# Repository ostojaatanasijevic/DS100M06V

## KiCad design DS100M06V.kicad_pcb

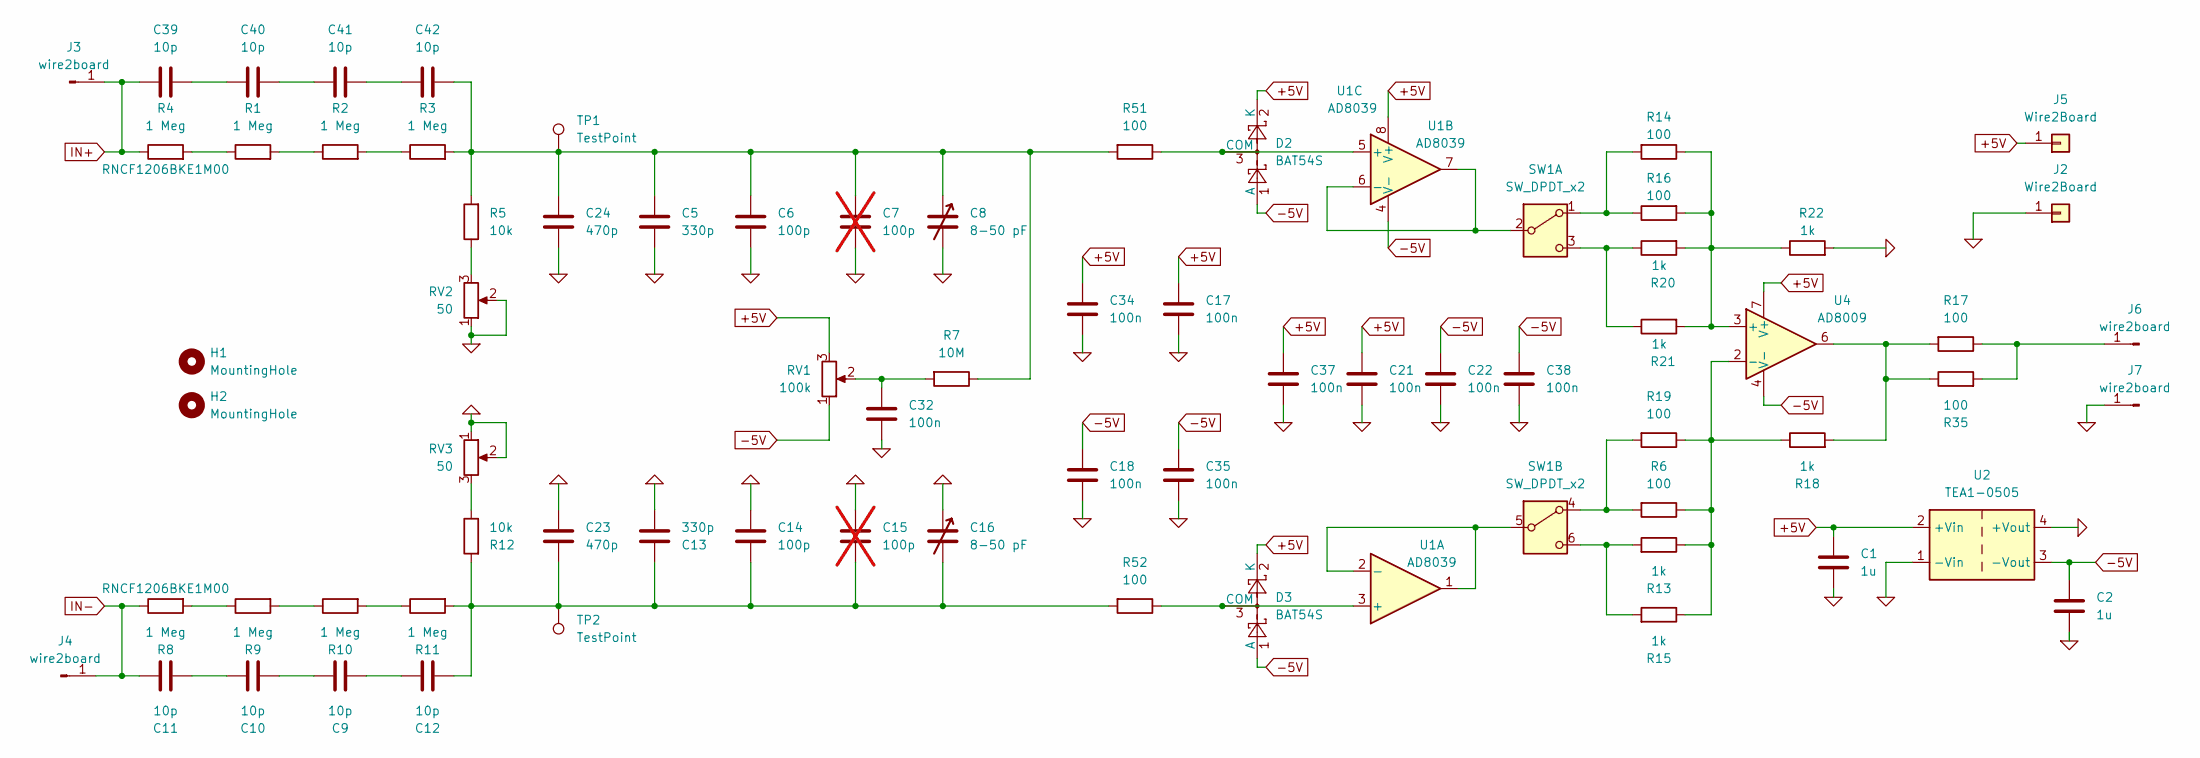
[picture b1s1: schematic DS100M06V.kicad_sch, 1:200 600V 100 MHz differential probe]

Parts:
C1, C2: 1u; R_0603_1608Metric_Pad0.98x0.95mm_HandSolder
C5, C13: 330p; R_0603_1608Metric_Pad0.98x0.95mm_HandSolder
C6, C14: 100p; R_0603_1608Metric_Pad0.98x0.95mm_HandSolder
C7, C15: 100p; R_0603_1608Metric_Pad0.98x0.95mm_HandSolder; not fitted
C8, C16: 8-50 pF; C_Trimmer_Murata_TZB4-A
C9, C10, C11, C12, C39, C40, C41, C42: 10p; R_0805_2012Metric
C17, C18, C21, C22, C32, C34, C35, C37, C38: 100n; R_0603_1608Metric_Pad0.98x0.95mm_HandSolder
C23, C24: 470p; R_0603_1608Metric_Pad0.98x0.95mm_HandSolder
D2, D3: BAT54S; SOT-23
H1, H2: MountingHole; MountingHole_3.2mm_M3
J2, J5: Wire2Board; SolderWire-0.127sqmm_1x01_D0.48mm_OD1mm
J3, J4, J6, J7: wire2board; SolderWire-0.25sqmm_1x01_D0.65mm_OD1.7mm
R1, R2, R3, R9, R10, R11: 1 Meg; R_1206_3216Metric_Pad1.30x1.75mm_HandSolder
R4, R8: 1 Meg; R_1206_3216Metric_Pad1.30x1.75mm_HandSolder; Partnumber RNCF1206BKE1M00
R5, R12: 10k; R_0603_1608Metric_Pad0.98x0.95mm_HandSolder
R6, R14, R16, R17, R19, R35, R51, R52: 100; R_0603_1608Metric_Pad0.98x0.95mm_HandSolder
R7: 10M; R_0603_1608Metric_Pad0.98x0.95mm_HandSolder
R13, R15, R18, R20, R21, R22: 1k; R_0603_1608Metric_Pad0.98x0.95mm_HandSolder
RV1: 100k; Potentiometer_Bourns_3296W_Vertical
RV2, RV3: 50; Potentiometer_Bourns_3296W_Vertical
SW1: SW_DPDT_x2; SW_CuK_JS202011CQN_DPDT_Straight
TP1, TP2: TestPoint; TestPoint_Pad_D2.0mm
U1: AD8039; SOIC-8_3.9x4.9mm_P1.27mm
U2: TEA1-0505; Converter_DCDC_TRACO_TEA1-xxxx_THT
U4: AD8009; SOIC-8_3.9x4.9mm_P1.27mm

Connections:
0: C1.2, C2.2, C5.1, C6.1, C7.1, C8.2, C13.1, C14.1, C15.1, C16.1, C17.1, C18.1, C21.1, C22.1, C23.1, C24.1, C32.1, C34.1, C35.1, C37.1, C38.1, J2.1, J7.1, R22.2, RV2.1, RV2.2, RV3.1, RV3.2, U2.1 (-Vin), U2.4 (+Vout)
+5V: C1.1, C17.2, C21.2, C34.2, C37.2, D2.2 (K), D3.2 (K), J5.1, RV1.3, U1.8 (V+), U2.2 (+Vin), U4.7 (V+)
-5V: C2.1, C18.2, C22.2, C35.2, C38.2, D2.1 (A), D3.1 (A), RV1.1, U1.4 (V-), U2.3 (-Vout), U4.4 (V-)
IN+: C39.2, J3.1, R4.1
IN-: C11.2, J4.1, R8.1
unnamed: C9.2, C10.1
unnamed: C10.2, C11.1
unnamed: C12.1, C13.2, C14.2, C15.2, C16.2, C23.2, R11.2, R12.2, R52.2, TP2.1
unnamed: C9.1, C12.2
unnamed: C5.2, C6.2, C7.2, C8.1, C24.2, C42.1, R3.2, R5.2, R7.1, R51.2, TP1.1
unnamed: C32.2, R7.2, RV1.2
unnamed: C39.1, C40.2
unnamed: C40.1, C41.2
unnamed: C41.1, C42.2
unnamed: D2.3 (COM), R51.1, U1.5 (+)
unnamed: D3.3 (COM), R52.1, U1.3 (+)
unnamed: J6.1, R17.1, R35.2
unnamed: R1.1, R4.2
unnamed: R1.2, R2.1
unnamed: R2.2, R3.1
unnamed: R5.1, RV2.3
unnamed: R8.2, R9.1
unnamed: R9.2, R10.1
unnamed: R10.2, R11.1
unnamed: R12.1, RV3.3
unnamed: R17.2, R18.2, R35.1, U4.6
unnamed: R14.2, R16.1, SW1.1 (A)
unnamed: SW1.2 (B), U1.6 (-), U1.7
unnamed: R20.1, R21.1, SW1.3 (C)
unnamed: R6.2, R19.2, SW1.4 (A)
unnamed: SW1.5 (B), U1.1, U1.2 (-)
unnamed: R13.2, R15.2, SW1.6 (C)
unnamed: R14.1, R16.2, R20.2, R21.2, R22.1, U4.3 (+)
unnamed: R6.1, R13.1, R15.1, R18.1, R19.1, U4.2 (-)

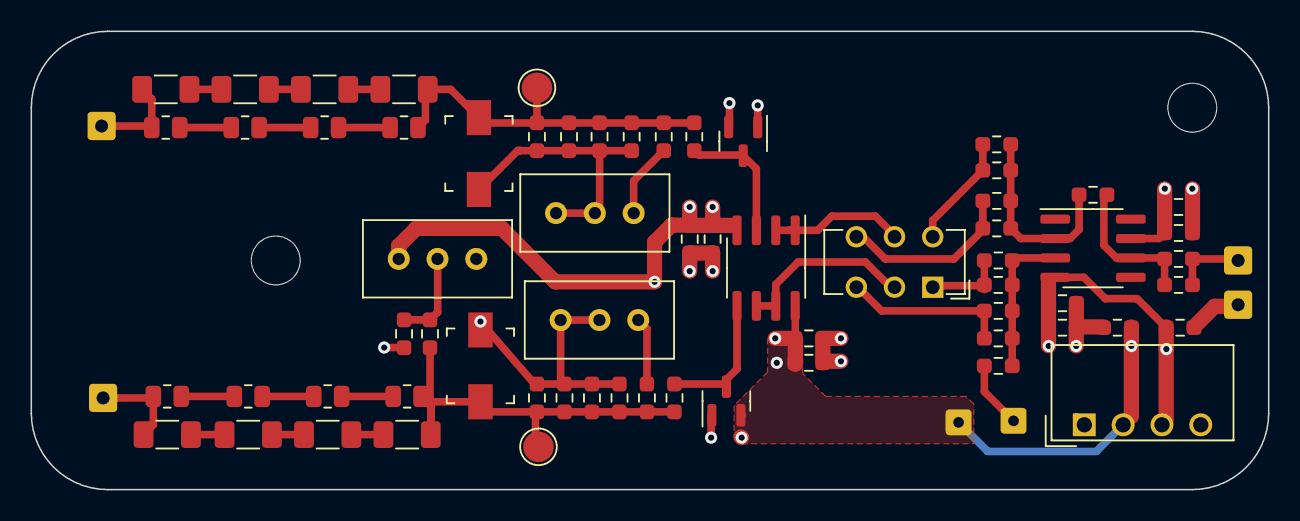
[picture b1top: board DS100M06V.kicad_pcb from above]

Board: 4 copper layers, 81.0 x 30.0 mm, 73 parts (0 on the bottom side), 34 nets.

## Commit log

2024-06-29 init
2024-06-29 Offset pot fixed.
